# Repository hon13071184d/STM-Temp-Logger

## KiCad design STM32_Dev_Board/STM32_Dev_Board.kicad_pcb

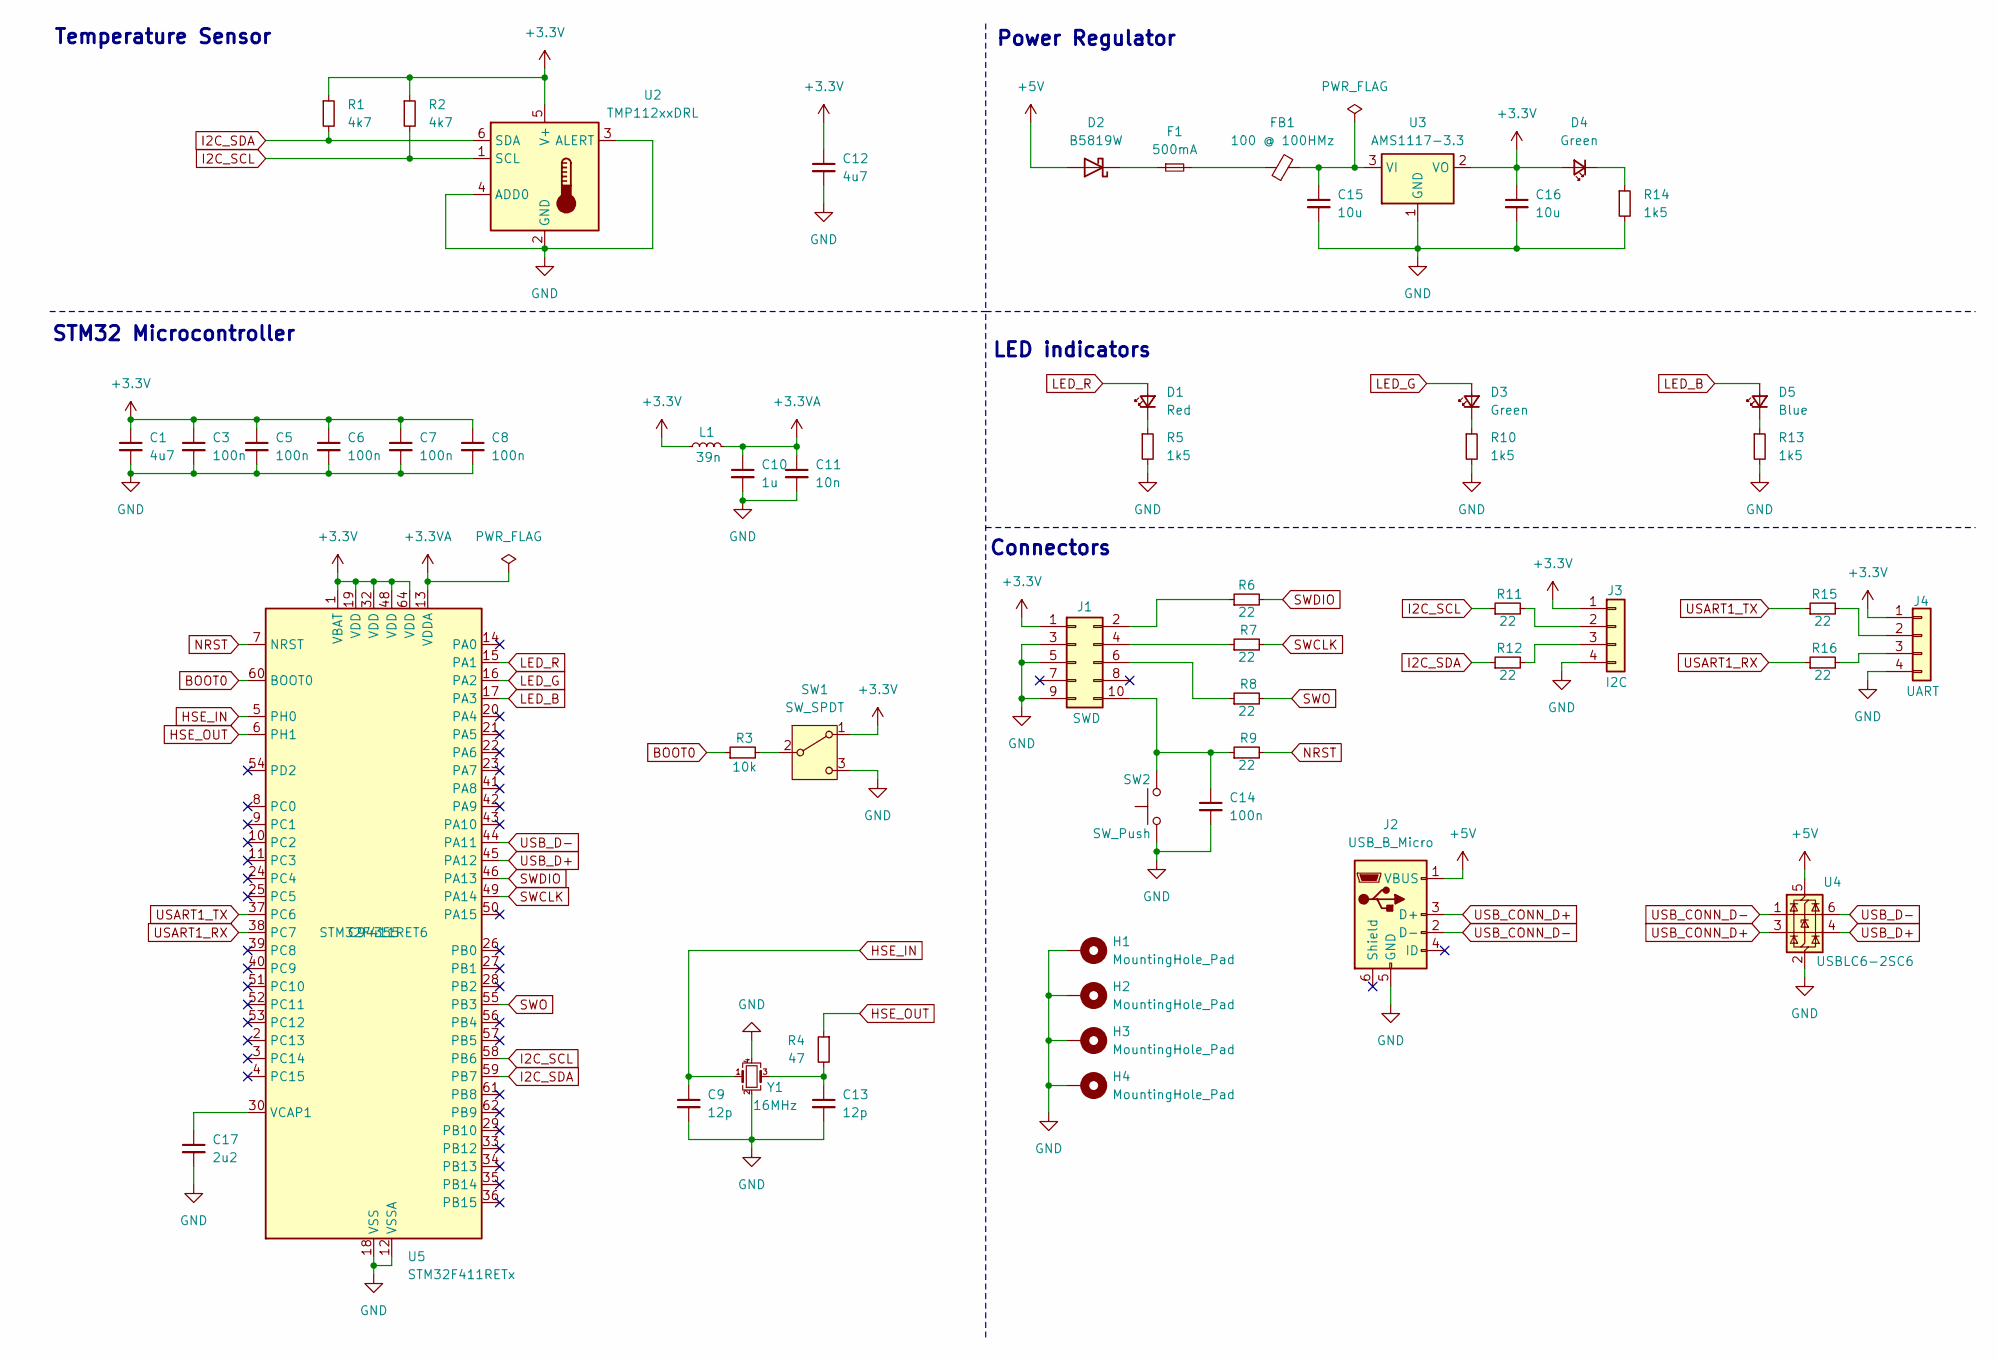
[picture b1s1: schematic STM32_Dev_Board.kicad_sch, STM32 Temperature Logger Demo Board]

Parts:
C1, C12: 4u7; C_0603_1608Metric; MPN CL10A475KO8NNNC; JLCPCB Part # C19666
C3, C5, C6, C7, C8, C14: 100n; C_0603_1608Metric; MPN CC0603KRX7R9BB104; JLCPCB Part # C14663
C9, C13: 12p; C_0603_1608Metric; MPN CL10C120JB8NNNC; JLCPCB Part # C38523
C10: 1u; C_0603_1608Metric; MPN CL10A105KB8NNNC; JLCPCB Part # C15849
C11: 10n; C_0603_1608Metric; MPN 0603B103K500NT; JLCPCB Part # C57112
C15, C16: 10u; C_1206_3216Metric; MPN CL31A106KBHNNNE; JLCPCB Part # C13585
C17: 2u2; C_0603_1608Metric; MPN CL10A225KO8NNNC; JLCPCB Part # C23630
D1: Red; LED_0603_1608Metric; MPN KT-0603R; JLCPCB Part # C2286
D2: B5819W; D_SOD-123; MPN B5819W SL; JLCPCB Part # C8598
D3, D4: Green; LED_0603_1608Metric; MPN KT-0603R; JLCPCB Part # C2286
D5: Blue; LED_0603_1608Metric; MPN KT-0603W; JLCPCB Part # C2290
F1: 500mA; Fuse_1206_3216Metric; MPN JK-NSMD050-13.2V; JLCPCB Part # C369159
FB1: 100 @ 100HMz; L_0805_2012Metric; MPN GZ2012D601TF; JLCPCB Part # C1017
H1, H2, H3, H4: MountingHole_Pad; MountingHole_2.2mm_M2_Pad_Via
J1: SWD; PinHeader_2x05_P1.27mm_Vertical_SMD; MPN FTSH-105-01-L-DV-K; JLCPCB Part # C5155080
J2: USB_B_Micro; USB_Micro-B_Molex-105133-0001; MPN 1051330001; JLCPCB Part # C782257
J3: I2C; Molex_PicoBlade_53048-0410_1x04_P1.25mm_Horizontal
J4: UART; Molex_PicoBlade_53048-0410_1x04_P1.25mm_Horizontal
L1: 39n; L_0402_1005Metric; MPN SDCL1005C39NJTDF; JLCPCB Part # C26443
R1, R2: 4k7; R_0603_1608Metric; MPN 0603WAF4701T5E; JLCPCB Part # C23162
R3: 10k; R_0402_1005Metric; MPN 0402WGF1002TCE; JLCPCB Part # C25744
R4: 47; R_0402_1005Metric; MPN 0402WGF470JTCE; JLCPCB Part # C25118
R5, R10, R13, R14: 1k5; R_0603_1608Metric; MPN 0603WAF1501T5E; JLCPCB Part # C22843
R6, R7, R8, R9, R11, R12, R15, R16: 22; R_0603_1608Metric; MPN 0603WAF220JT5E; JLCPCB Part # C23345
SW1: SW_SPDT; SW_SPDT_PCM12; MPN PCM12SMTR; JLCPCB Part # C221841
SW2: SW_Push; SW_SPST_B3S-1000; MPN B3S-1000; JLCPCB Part # C2733655
U2: TMP112xxDRL; SOT-563; MPN TMP112AIDRLR; JLCPCB Part # C28927
U3: AMS1117-3.3; SOT-223-3_TabPin2; MPN AMS1117-3.3; JLCPCB Part # C6186
U4: USBLC6-2SC6; SOT-23-6; MPN USBLC6-2SC6; JLCPCB Part # C7519
U5: STM32F411RETx; LQFP-64_10x10mm_P0.5mm; MPN STM32F411RET6; JLCPCB Part # C94355
Y1: 16MHz; Crystal_SMD_3225-4Pin_3.2x2.5mm; MPN X322516MLB4SI; JLCPCB Part # C13738

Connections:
+3.3V: C1.1, C3.1, C5.1, C6.1, C7.1, C8.1, C12.1, C16.1, D4.2 (A), J1.1, J3.1, J4.1, L1.1, R1.1, R2.1, SW1.1 (A), U2.5 (V+), U3.2 (VO), U5.1 (VBAT), U5.19 (VDD), U5.32 (VDD), U5.48 (VDD), U5.64 (VDD)
+3.3VA: C10.1, C11.1, L1.2, U5.13 (VDDA)
+5V: D2.2 (A), J2.1 (VBUS), U4.5 (VBUS)
BOOT0: R3.1, U5.60 (BOOT0)
GND: C1.2, C3.2, C5.2, C6.2, C7.2, C8.2, C9.2, C10.2, C11.2, C12.2, C13.2, C14.2, C15.2, C16.2, C17.2, H1.1, H2.1, H3.1, H4.1, J1.3, J1.5, J1.9, J2.5 (GND), J3.4, J4.4, R5.2, R10.2, R13.2, R14.2, SW1.3 (C), SW2.1, U2.2 (GND), U2.3 (ALERT), U2.4 (ADD0), U3.1 (GND), U4.2 (GND), U5.12 (VSSA), U5.18 (VSS), U5.31 (VSS), U5.47 (VSS), U5.63 (VSS), Y1.2, Y1.4
HSE_IN: C9.1, U5.5 (PH0), Y1.1
HSE_OUT: R4.1, U5.6 (PH1)
I2C_SCL: R2.2, R11.1, U2.1 (SCL), U5.58 (PB6)
I2C_SDA: R1.2, R12.1, U2.6 (SDA), U5.59 (PB7)
LED_B: D5.2 (A), U5.17 (PA3)
LED_G: D3.2 (A), U5.16 (PA2)
LED_R: D1.2 (A), U5.15 (PA1)
NRST: R9.2, U5.7 (NRST)
unnamed: C13.1, R4.2, Y1.3
unnamed: D1.1 (K), R5.1
unnamed: D2.1 (K), F1.1
unnamed: D3.1 (K), R10.1
unnamed: D4.1 (K), R14.1
unnamed: D5.1 (K), R13.1
unnamed: F1.2, FB1.1
unnamed: J1.2, R6.1
unnamed: J1.4, R7.1
unnamed: J1.6, R8.1
unnamed: C14.1, J1.10, R9.1, SW2.2
unnamed: J3.2, R11.2
unnamed: J3.3, R12.2
unnamed: J4.2, R15.2
unnamed: J4.3, R16.2
unnamed: R3.2, SW1.2 (B)
unnamed: C15.1, FB1.2, U3.3 (VI)
unnamed: C17.1, U5.30 (VCAP1)
SWCLK: R7.2, U5.49 (PA14)
SWDIO: R6.2, U5.46 (PA13)
SWO: R8.2, U5.55 (PB3)
USART1_RX: R16.1, U5.38 (PC7)
USART1_TX: R15.1, U5.37 (PC6)
USB_CONN_D+: J2.3 (D+), U4.3 (I/O2)
USB_CONN_D-: J2.2 (D-), U4.1 (I/O1)
USB_D+: U4.4 (I/O2), U5.45 (PA12)
USB_D-: U4.6 (I/O1), U5.44 (PA11)

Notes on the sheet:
LED indicators
STM32 Microcontroller
Connectors
Temperature Sensor
Power Regulator

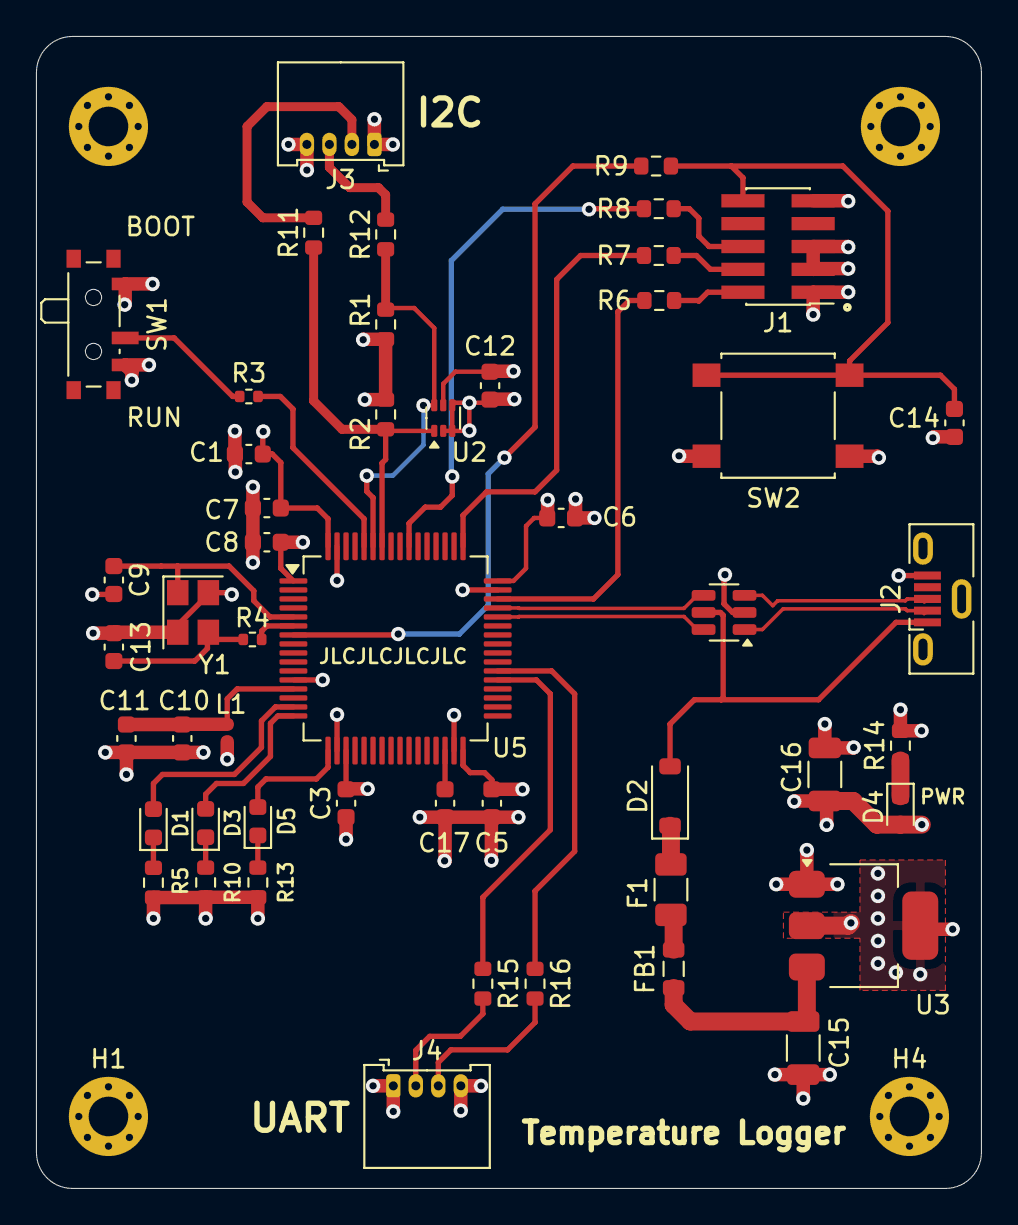
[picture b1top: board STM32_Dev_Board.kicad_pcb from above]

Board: 4 copper layers, 52.5 x 64.0 mm, 54 parts (0 on the bottom side), 40 nets.

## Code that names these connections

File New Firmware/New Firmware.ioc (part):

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Mcu.Name=STM32F411R(C-E)Tx
Mcu.Package=LQFP64
Mcu.UserName=STM32F411RETx
PA1.GPIOParameters=GPIO_Label
PA1.GPIO_Label=LED_R
PA1.Signal=GPIO_Output
PA11.Mode=Device_Only
PA11.Signal=USB_OTG_FS_DM
PA12.Mode=Device_Only
PA12.Signal=USB_OTG_FS_DP
PA13.Mode=Trace_Asynchronous_SW
PA13.Signal=SYS_JTMS-SWDIO
PA14.Mode=Trace_Asynchronous_SW
PA14.Signal=SYS_JTCK-SWCLK
PA2.GPIOParameters=GPIO_Label
PA2.GPIO_Label=LED_G
PA2.Signal=GPIO_Output
PA3.GPIOParameters=GPIO_Label
PA3.GPIO_Label=LED_B
PA3.Signal=GPIO_Output
PB3.Mode=Trace_Asynchronous_SW
PB3.Signal=SYS_JTDO-SWO
PB6.Mode=I2C
PB6.Signal=I2C1_SCL
PB7.Mode=I2C
PB7.Signal=I2C1_SDA
PC6.Mode=Asynchronous
PC6.Signal=USART6_TX
PC7.Mode=Asynchronous
PC7.Signal=USART6_RX
PH0\ -\ OSC_IN.Mode=HSE-External-Oscillator
PH0\ -\ OSC_IN.Signal=RCC_OSC_IN
PH1\ -\ OSC_OUT.Mode=HSE-External-Oscillator
PH1\ -\ OSC_OUT.Signal=RCC_OSC_OUT
RCC.HSE_VALUE=25000000
RCC.SYSCLKFreq_VALUE=16000000
board=custom
